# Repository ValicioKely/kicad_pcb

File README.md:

# kicad_pcb
Store kicad project

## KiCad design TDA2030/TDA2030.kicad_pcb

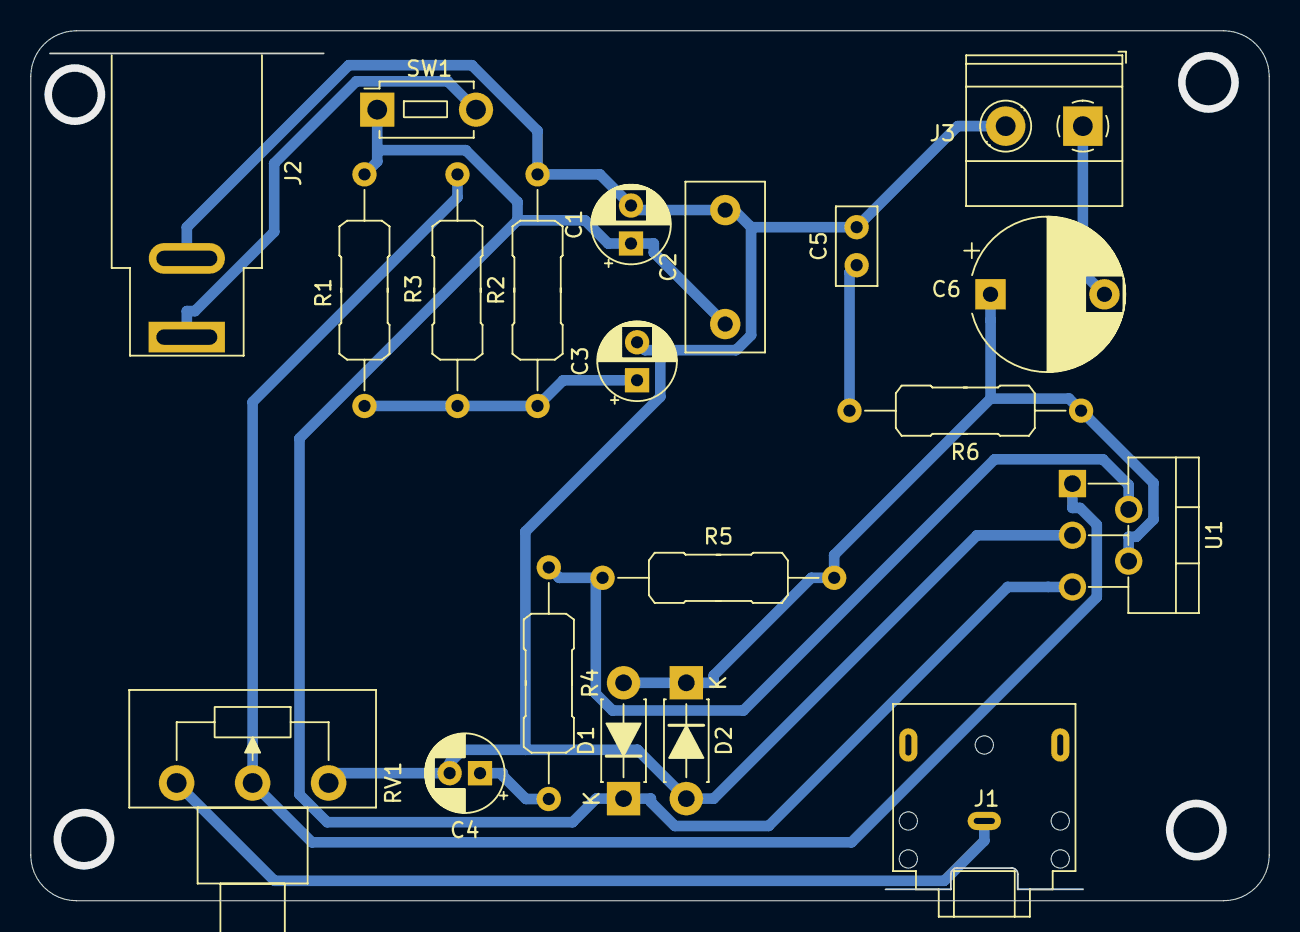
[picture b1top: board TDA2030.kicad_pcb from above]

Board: 2 copper layers, 81.4 x 57.2 mm, 20 parts (0 on the bottom side), 11 nets.

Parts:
C1: 100uF; CP_Radial_D5.0mm_P2.50mm
C2: 100uF; C_Disc_D11.0mm_W5.0mm_P7.50mm
C3: 22uF; CP_Radial_D5.0mm_P2.50mm
C4: 1uF; CP_Radial_D5.0mm_P2.00mm
C5: 220nF; C_Disc_D5.0mm_W2.5mm_P2.50mm
C6: 2000uF; CP_Radial_D10.0mm_P7.50mm
D1, D2: 1N4007; D_DO-41_SOD81_P7.62mm_Horizontal
J1: AudioJack2_Ground; Jack_3.5mm_CUI_SJ1-3523N_Horizontal
J2: Barrel_Jack; BarrelJack_SwitchcraftConxall_RAPC10U_Horizontal
J3: HP 42; TerminalBlock_Phoenix_MKDS-1,5-2-5.08_1x02_P5.08mm_Horizont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
R1, R2, R3: 100K; R_Axial_DIN0309_L9.0mm_D3.2mm_P15.24mm_Horizontal
R4: 47K; R_Axial_DIN0309_L9.0mm_D3.2mm_P15.24mm_Horizontal
R5: 150K; R_Axial_DIN0309_L9.0mm_D3.2mm_P15.24mm_Horizontal
R6: 1; R_Axial_DIN0309_L9.0mm_D3.2mm_P15.24mm_Horizontal
RV1: 10k - 22K; Potentiometer_Piher_T-16H_Single_Horizontal
SW1: Power; SW_PUSH_1P1T_6x3.5mm_H4.3_APEM_MJTP1243
U1: TDA2030; TO-220-5_P3.4x3.7mm_StaggerOdd_Lead3.8mm_Vertical

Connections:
GNDREF: C1.2, C2.2, C3.2, C4.2, C5.2, D2.2 (A), J2.2, J3.2, R2.2, RV1.3, U1.3 (-Vs)
unnamed: C3.1, R1.2, R2.1, R3.1
unnamed: C4.1, R4.2
unnamed: C5.1, R6.2
unnamed: C6.1, D1.2 (A), D2.1 (K), R5.2, R6.1, U1.4
unnamed: J1.S, RV1.1
unnamed: C6.2, J3.1
unnamed: J2.1, SW1.2 (B)
unnamed: R4.1, R5.1, U1.2 (-)
V+: R3.2, RV1.2, U1.1 (+)
VCC: C1.1, C2.1, D1.1 (K), R1.1, SW1.1 (A), U1.5 (+Vs)

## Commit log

2025-04-19 Create TDA 2030 pcb board
2025-04-19 Schema
2025-04-19 Assing footprint
2025-04-19 Routing PCB
2025-04-19 Adding vias for fixation
2025-04-19 routing
